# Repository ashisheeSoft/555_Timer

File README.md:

# 555_Timer
A KiCaD design for simple 555 timer circuit..
Download 555_timer.zip file and Open it with the KiCad software.
Gerber files are also given in order to plot this on real pcb

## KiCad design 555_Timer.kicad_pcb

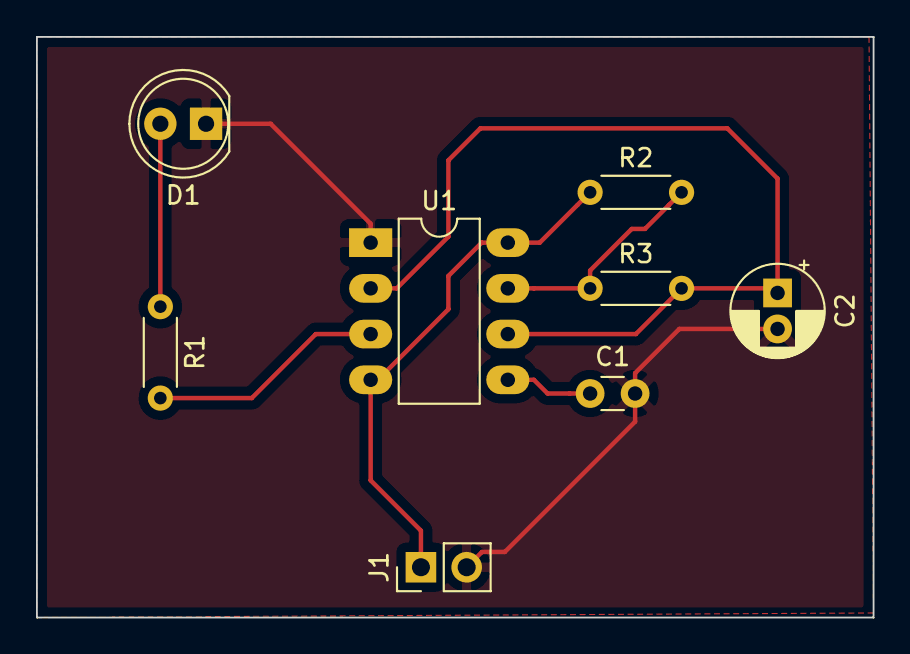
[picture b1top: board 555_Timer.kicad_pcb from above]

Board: 2 copper layers, 46.5 x 32.3 mm, 8 parts (0 on the bottom side), 7 nets.

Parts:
C1: 100nF; C_Disc_D3.0mm_W1.6mm_P2.50mm
C2: 47uF; CP_Radial_D5.0mm_P2.00mm
D1: LED; LED_D5.0mm
J1: Conn_01x02_Female; PinHeader_1x02_P2.54mm_Vertical
R1: 330; R_Axial_DIN0204_L3.6mm_D1.6mm_P5.08mm_Horizontal
R2: 10k; R_Axial_DIN0204_L3.6mm_D1.6mm_P5.08mm_Horizontal
R3: 100k; R_Axial_DIN0204_L3.6mm_D1.6mm_P5.08mm_Horizontal
U1: NE555; DIP-8_W7.62mm_LongPads

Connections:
+5V: J1.1, R2.1, U1.4, U1.8
GND: C1.2, C2.2, D1.1, J1.2, U1.1
unnamed: C1.1, U1.5
unnamed: C2.1, R3.2, U1.2, U1.6
unnamed: D1.2, R1.1
unnamed: R1.2, U1.3
unnamed: R2.2, R3.1, U1.7
